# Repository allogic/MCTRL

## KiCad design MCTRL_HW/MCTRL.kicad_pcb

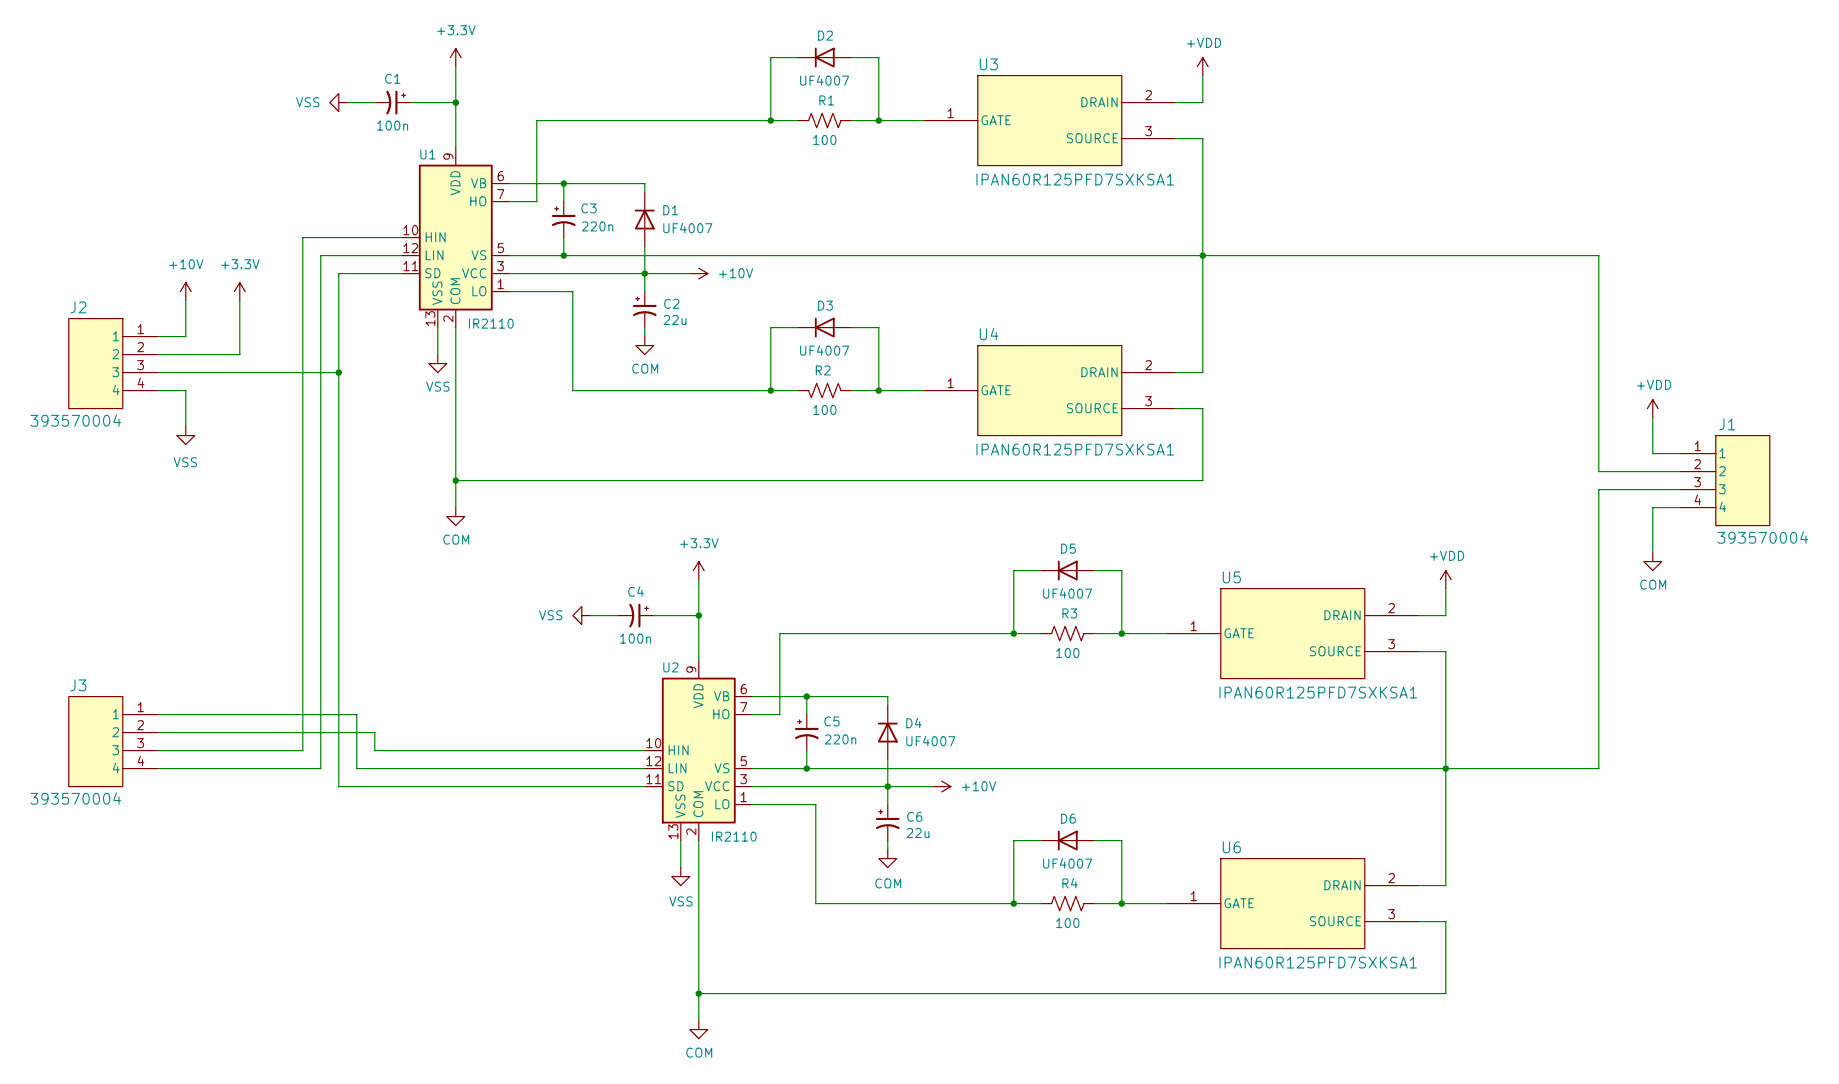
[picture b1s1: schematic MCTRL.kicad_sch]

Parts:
C1, C4: 100n; UUP1H0R1MCL1GS
C2, C6: 22u; EEEFK1H220P
C3, C5: 220n; UWP1HR22MCL1GB
D1, D2, D3, D4, D5, D6: UF4007; D_DO-15_P12.70mm_Horizontal
J1, J2, J3: 393570004
R1, R2, R3, R4: 100; R_Axial_DIN0309_L9.0mm_D3.2mm_P12.70mm_Horizontal
U1, U2: IR2110; DIP-14_W7.62mm
U3, U4, U5, U6: IPAN60R125PFD7SXKSA1

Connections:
+3.3V: C1.1, C4.1, J2.2, U1.9 (VDD), U2.9 (VDD)
+10V: C2.1, C6.1, D1.2 (A), D4.2 (A), J2.1, U1.3 (VCC), U2.3 (VCC)
+VDD: J1.1, U3.2 (DRAIN), U5.2 (DRAIN)
COM: C2.2, C6.2, J1.4, U1.2 (COM), U2.2 (COM), U4.3 (SOURCE), U6.3 (SOURCE)
unnamed: C3.1, D1.1 (K), U1.6 (VB)
unnamed: D2.2 (A), R1.2, U3.1 (GATE)
unnamed: D2.1 (K), R1.1, U1.7 (HO)
unnamed: D3.2 (A), R2.1, U4.1 (GATE)
unnamed: D3.1 (K), R2.2, U1.1 (LO)
unnamed: C5.1, D4.1 (K), U2.6 (VB)
unnamed: D5.2 (A), R3.2, U5.1 (GATE)
unnamed: D5.1 (K), R3.1, U2.7 (HO)
unnamed: D6.2 (A), R4.2, U6.1 (GATE)
unnamed: D6.1 (K), R4.1, U2.1 (LO)
unnamed: J3.3, U1.10 (HIN)
unnamed: J3.4, U1.12 (LIN)
unnamed: J2.3, U1.11 (SD), U2.11 (SD)
unnamed: C3.2, J1.2, U1.5 (VS), U3.3 (SOURCE), U4.2 (DRAIN)
unnamed: J3.2, U2.10 (HIN)
unnamed: J3.1, U2.12 (LIN)
unnamed: C5.2, J1.3, U2.5 (VS), U5.3 (SOURCE), U6.2 (DRAIN)
VSS: C1.2, C4.2, J2.4, U1.13 (VSS), U2.13 (VSS)

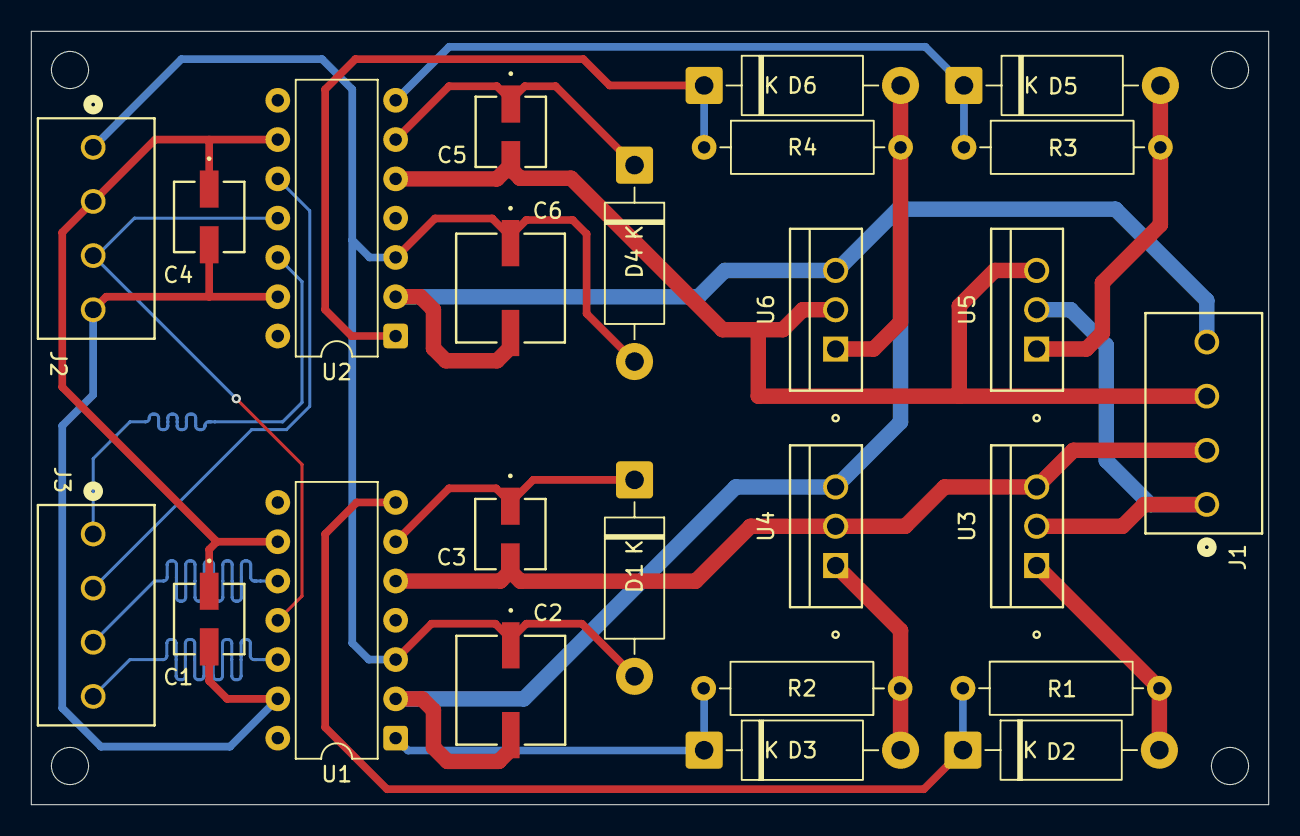
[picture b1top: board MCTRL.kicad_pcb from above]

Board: 2 copper layers, 80.0 x 50.0 mm, 25 parts (0 on the bottom side), 22 nets.

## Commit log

2026-05-04 Added se basics
2026-05-04 more changes
2026-05-06 Unfinished PCB
2026-05-07 Finished first proto
2026-05-10 Some firmware changes
2026-05-10 stupid git tokens
2026-05-10 some foo
2026-05-10 Some changes
2026-05-15 good firmware
2026-05-15 Added picocom
2026-05-31 Fixed diode direction
